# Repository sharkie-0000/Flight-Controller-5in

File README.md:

# 5-Inch Autonomous Wall-Inspection Flight Controller

A custom 4-layer drone flight controller designed for autonomous infrastructure inspection (inspecting building facades, concrete structures, bridges, and industrial indoor spaces where GPS is completely denied). It was a great way for me to explore high-speed embedded design, learn 4-layer PCB routing in KiCad, and solve real-world signal integrity and power challenges.

# How its works

This board is a custom-designed flight controller for autonomous GPS-denied drone navigation. It is based on the 480MHz ARM Cortex-M7 STM32H743VIT6 microcontroller and industrial-grade low-noise sensors.

- **Power & Protection:** Accepts 3S–6S LiPo battery power. An SMBJ28A TVS clamp and low-ESR bulk capacitance protect against motor regenerative braking spikes. A TPS54302 synchronous buck converter steps down to 5V @ 3A, while a dedicated ultra-low-noise MIC5219-3.3 LDO isolates sensitive sensor rails from switching noise.
- **Processing & Memory:** The STM32H743VIT6 serves as the main brain. It runs at 480MHz from an external 25MHz crystal, backed by a W25Q128 16MB SPI NOR Flash chip for high-rate Blackbox flight logging.
- **Dual-Navigation & Sensing:** Features an ICM-42688-P 6-axis IMU over high-speed SPI1 and a DPS310 barometer over I2C1. For indoor GPS-denied flight, dedicated ports connect a forward-facing Time-of-Flight (ToF) LiDAR for wall standoff tracking and a downward Optical Flow camera for hover holding.
- **Actuation & Companion Link:** Connects to standard 4-in-1 ESCs via DShot600 motor outputs (`MOTOR1`–`4`). A high-speed MAVLink UART communicates with an onboard companion computer (Raspberry Pi / NVIDIA Jetson), while an onboard 2N7002 MOSFET circuit synchronously triggers an inspection camera shutter or strobe.

```text
[ LiPo 3S-6S ] ──► [ SMBJ28A TVS ] ──► [ TPS54302 Buck (5V 3A) ] ──5V──► [ MIC5219 (3.3V LDO) ] ──3.3V──┐
                                                 │                                                         ▼
                                          5V Peripherals                                            [ STM32H743 ]
                                                 │                                                   (480MHz MCU)
                                                 │                                                         │
   ┌───────────────────────┬─────────────────────┼─────────────────────────┬───────────────────────────────┤
   │ (SPI1)                │ (I2C1)              │ (SPI2)                  │ (UARTs)                       │ (TIM PWM)
   ▼                       ▼                     ▼                         ▼                               ▼
[ ICM-42688-P ]       [ DPS310 ]            [ W25Q128 ]          [ Forward Wall ToF ]               [ 4-in-1 ESC ]
  (6-Axis IMU)         (Baro)               (Blackbox)           [ Downward Flow    ]               (DShot Motors)
                                                                 [ Outdoor GPS/Mag  ]
                                                                 [ Jetson / Pi MAV  ]
                                                                 [ ELRS Receiver    ]
```

# Images:

## 3d

## Schematic

## PCB

## Components

- **Total Physical Components:** 51
- **Capacitors:** 24 (Bulk 470µF electrolytic, 22µF, 10µF, 2.2µF VCAP, 100nF decoupling, 18pF crystal caps)
- **Resistors:** 8 (Precision 0.1% voltage divider, USB-C 5.1k pull-downs, I2C 2.2k pull-ups)
- **Inductor:** 1 (4.7µH 4.5A shielded power inductor)
- **Crystals / Oscillators:** 1 (25.000MHz HSE crystal)
- **Microcontroller:** 1 (STM32H743VIT6 ARM Cortex-M7 LQFP-100)
- **Sensors:** 2 (ICM-42688-P 6-axis IMU, DPS310 precision barometer)
- **Memory:** 1 (W25Q128 16MB SPI NOR Flash)
- **Power ICs:** 2 (TPS54302 5V 3A buck converter, MIC5219-3.3 low-noise LDO)
- **MOSFETs / Diodes:** 3 (SMBJ28A TVS clamp, 2x 2N7002 N-channel FETs for buzzer & camera strobe)
- **Connectors / Headers:** 8 (USB-C 16-pin, JST-SH 8-pin ESC, JST-SH 6-pin GPS, 3x JST-SH 4-pin for ToF/Flow/MAVLink, SWD header, Buzzer pads)
- **Bare PCB Fabrication:** 5x 4-layer FR-4 boards (JLCPCB 36x36mm, JLC04161H-7628 stackup)

## BOM

| Qty | Component | Selected Part | Supplier | LCSC Part Number | Unit Price (USD) | Order Cost (USD) |
| :-: | :--- | :--- | :-: | :-: | --: | --: |
| 1 | STM32H743VIT6 MCU (Cortex-M7 480MHz, 2MB Flash, LQFP-100) | STM32H743VIT6 | LCSC | [C143110](https://www.lcsc.com/product-detail/C143110.html) | $11.20 | $11.20 |
| 1 | ICM-42688-P 6-Axis Low-Noise IMU (LGA-14) | ICM-42688-P | LCSC | [C2842426](https://www.lcsc.com/product-detail/C2842426.html) | $2.85 | $2.85 |
| 1 | DPS310 High-Precision Barometer (8-LGA) | DPS310XTSA1 | LCSC | [C155453](https://www.lcsc.com/product-detail/C155453.html) | $1.45 | $1.45 |
| 1 | W25Q128 16MB SPI NOR Flash (SOIC-8) | W25Q128JVSIQ | LCSC | [C97521](https://www.lcsc.com/product-detail/C97521.html) | $0.65 | $0.65 |
| 1 | TPS54302 5V 3A Synchronous Buck Converter (SOT-23-6) | TPS54302DDCR | LCSC | [C115848](https://www.lcsc.com/product-detail/C115848.html) | $0.72 | $0.72 |
| 1 | MIC5219-3.3 Ultra-Low-Noise LDO (SOT-23-5) | MIC5219-3.3YM5 | LCSC | [C7899](https://www.lcsc.com/product-detail/C7899.html) | $0.38 | $0.38 |
| 1 | SMBJ28A TVS Diode Clamp 600W (SMB) | SMBJ28A | LCSC | [C8536](https://www.lcsc.com/product-detail/C8536.html) | $0.12 | $0.12 |
| 1 | 4.7uH 4.5A Shielded Power Inductor (SMD 7x7mm) | NR8040T4R7N | LCSC | [C10452](https://www.lcsc.com/product-detail/C10452.html) | $0.35 | $0.35 |
| 1 | 25.000MHz High-Speed External Crystal (3225) | X322525MOB4SI | LCSC | [C9002](https://www.lcsc.com/product-detail/C9002.html) | $0.18 | $0.18 |
| 2 | 2N7002 N-Channel MOSFET 60V 300mA (SOT-23) | 2N7002 | LCSC | [C8502](https://www.lcsc.com/product-detail/C8502.html) | $0.04 | $0.08 |
| 1 | USB-C 16-Pin Receptacle (SMD+DIP) | TYPE-C-31-M-12 | LCSC | [C165948](https://www.lcsc.com/product-detail/C165948.html) | $0.28 | $0.28 |
| 1 | JST-SH 8-Pin Horizontal 1.0mm (4-in-1 ESC) | SM08B-SRSS-TB | LCSC | [C160404](https://www.lcsc.com/product-detail/C160404.html) | $0.22 | $0.22 |
| 1 | JST-SH 6-Pin Horizontal 1.0mm (GPS/Compass) | SM06B-SRSS-TB | LCSC | [C160403](https://www.lcsc.com/product-detail/C160403.html) | $0.18 | $0.18 |
| 2 | JST-SH 4-Pin Horizontal 1.0mm (ToF & RC) | SM04B-SRSS-TB | LCSC | [C160401](https://www.lcsc.com/product-detail/C160401.html) | $0.15 | $0.30 |
| 1 | JST-SH 4-Pin Horizontal 1.0mm (Optical Flow) | SM04B-SRSS-TB | LCSC | [C160401](https://www.lcsc.com/product-detail/C160401.html) | $0.15 | $0.15 |
| 1 | JST-SH 4-Pin Horizontal 1.0mm (MAVLink Jetson) | SM04B-SRSS-TB | LCSC | [C160401](https://www.lcsc.com/product-detail/C160401.html) | $0.15 | $0.15 |
| 1 | 470uF 35V Low-ESR Bulk Electrolytic Capacitor | Radial Low-ESR | LCSC | [C134444](https://www.lcsc.com/product-detail/C134444.html) | $0.25 | $0.25 |
| 2 | 22uF 10V Ceramic Capacitor (0805 X5R) | 22uF 10V 0805 | LCSC | [C45783](https://www.lcsc.com/product-detail/C45783.html) | $0.05 | $0.10 |
| 1 | 10uF 50V Ceramic Capacitor (1206 X7R) | 10uF 50V 1206 | LCSC | [C13585](https://www.lcsc.com/product-detail/C13585.html) | $0.08 | $0.08 |
| 2 | 2.2uF 10V Ceramic Capacitor (0603 X7R - VCAP) | 2.2uF 10V 0603 | LCSC | [C23630](https://www.lcsc.com/product-detail/C23630.html) | $0.03 | $0.06 |
| 14 | 100nF 16V Ceramic Decoupling Capacitor (0402 X7R) | 100nF 16V 0402 | LCSC | [C1525](https://www.lcsc.com/product-detail/C1525.html) | $0.005 | $0.07 |
| 2 | 18pF 50V Crystal Load Capacitor (0402 C0G) | 18pF 50V 0402 | LCSC | [C1549](https://www.lcsc.com/product-detail/C1549.html) | $0.005 | $0.01 |
| 1 | 10k 0.1% Precision Voltage Divider Resistor (0603) | 10k 0.1% 0603 | LCSC | [C25744](https://www.lcsc.com/product-detail/C25744.html) | $0.03 | $0.03 |
| 1 | 1.0k 0.1% Precision Voltage Divider Resistor (0603) | 1.0k 0.1% 0603 | LCSC | [C25741](https://www.lcsc.com/product-detail/C25741.html) | $0.03 | $0.03 |
| 2 | 5.1k 1% USB-C CC Pulldown Resistor (0402) | 5.1k 1% 0402 | LCSC | [C25905](https://www.lcsc.com/product-detail/C25905.html) | $0.004 | $0.01 |
| 2 | 2.2k 1% I2C Bus Pullup Resistor (0402) | 2.2k 1% 0402 | LCSC | [C25879](https://www.lcsc.com/product-detail/C25879.html) | $0.004 | $0.01 |
| 2 | LED 0805 SMD (Blue Power / Green Armed) | LED 0805 | LCSC | [C84256](https://www.lcsc.com/product-detail/C84256.html) | $0.02 | $0.04 |
| 1 | 5V Active Buzzer Header / Pads | PinHeader 1x02 1.27mm | LCSC | [C2938](https://www.lcsc.com/product-detail/C2938.html) | $0.05 | $0.05 |
| 1 | Camera Shutter / Strobe Header | PinHeader 1x03 2.54mm | LCSC | [C2337](https://www.lcsc.com/product-detail/C2337.html) | $0.08 | $0.08 |
| 1 | SWD Debug Header | PinHeader 1x04 1.27mm | LCSC | [C2939](https://www.lcsc.com/product-detail/C2939.html) | $0.10 | $0.10 |
| 5 | Custom 4-Layer PCB (36x36mm, JLCPCB JLC04161H-7628 Stackup) | Custom PCB | JLCPCB | [JLCPCB](https://jlcpcb.com) | $1.00 | $5.00 |
| **—** | **Total Components Cost** | | **LCSC** | | | **$20.18** |
| **—** | **Total Procurement Cost (Components + 5x PCBs)** | | **LCSC + JLCPCB** | | | **~$25.18** |

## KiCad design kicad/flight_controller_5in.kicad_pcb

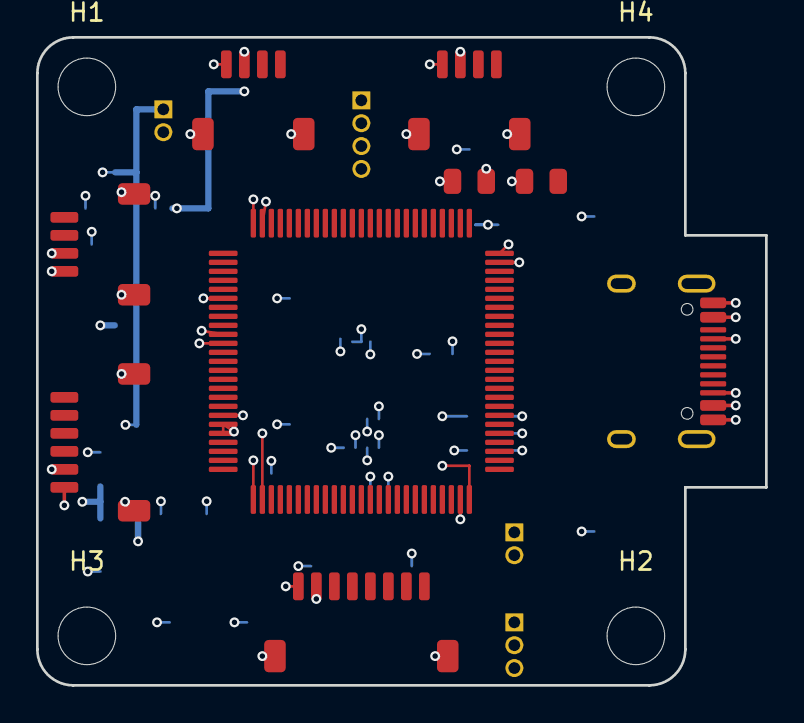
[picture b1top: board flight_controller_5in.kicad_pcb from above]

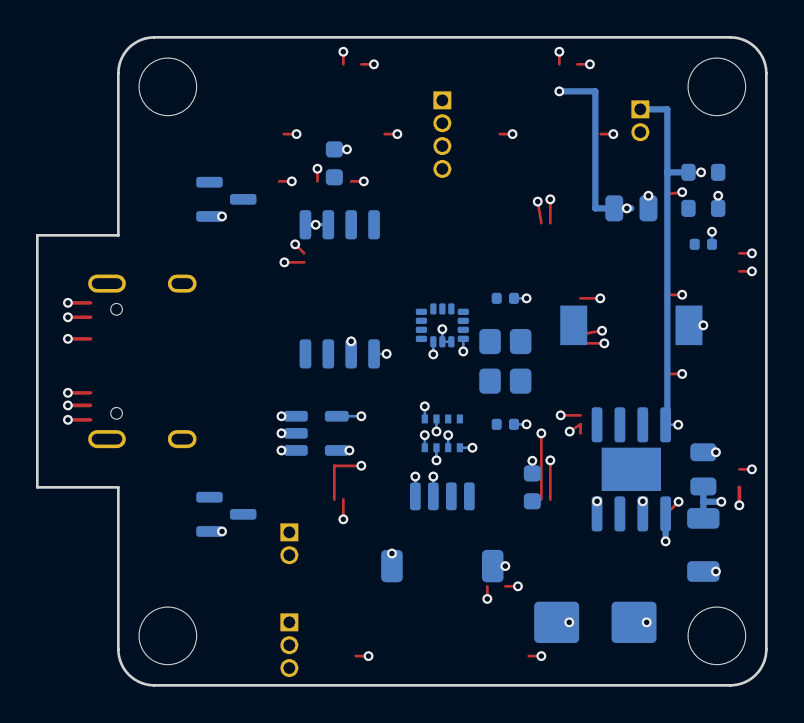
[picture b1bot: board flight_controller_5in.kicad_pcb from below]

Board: 4 copper layers, 40.5 x 36.0 mm, 38 parts (24 on the bottom side), 46 nets.

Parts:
BZ1: Buzzer Pads; PinHeader_1x02_P1.27mm_Vertical
C1: 22uF 50V Bulk; C_1206_3216Metric
C2: 10uF 50V; C_0805_2012Metric
C3: 22uF 10V; C_0805_2012Metric
C7: 100nF ADC; C_0402_1005Metric
C9, C10: 18pF; C_0402_1005Metric
C11: 2.2uF VCAP1; C_0603_1608Metric
C12: 2.2uF VCAP2; C_0603_1608Metric
D1: SMBJ28A TVS; D_SMB
D2: Blue 3.3V; LED_0805_2012Metric
D3: Green Armed; LED_0805_2012Metric
H1, H2, H3, H4: M3; MountingHole_3.2mm_M3
J_BAT: VBAT Pads; PinHeader_1x02_P1.27mm_Vertical
J_ESC: 4-in-1 ESC; JST_SH_SM08B-SRSS-TB_1x08-1MP_P1.00mm_Horizontal
J_FLOW: Optical Flow; JST_SH_SM04B-SRSS-TB_1x04-1MP_P1.00mm_Horizontal
J_GPS: GPS & Compass; JST_SH_SM06B-SRSS-TB_1x06-1MP_P1.00mm_Horizontal
J_MAVLINK: Companion MAVLink; JST_SH_SM04B-SRSS-TB_1x04-1MP_P1.00mm_Horizontal
J_RC: ELRS RC; JST_SH_SM04B-SRSS-TB_1x04-1MP_P1.00mm_Horizontal
J_STROBE: Camera Strobe; PinHeader_1x03_P1.27mm_Vertical
J_SWD: SWD Debug; PinHeader_1x04_P1.27mm_Vertical
J_USB: USB-C; USB_C_Receptacle_HRO_TYPE-C-31-M-12
J_WALL_TOF: ToF LiDAR; JST_SH_SM04B-SRSS-TB_1x04-1MP_P1.00mm_Horizontal
L1: 4.7uH Inductor; L_7.3x7.3_H3.5
Q1: 2N7002 Strobe; SOT-23
Q2: 2N7002 Buzzer; SOT-23
R1: 10k 0.1%; R_0603_1608Metric
R2: 1k 0.1%; R_0603_1608Metric
U1: TPS54302 (5V 3A); SOIC-8-1EP_3.9x4.9mm_P1.27mm_EP2.41x3.3mm
U2: MIC5219-3.3; SOT-23-5
U3: STM32H743VIT6; LQFP-100_14x14mm_P0.5mm
U4: ICM-42688-P; LGA-14_3x2.5mm_P0.5mm_LayoutBorder3x4y
U5: DPS310; Bosch_LGA-8_2x2.5mm_P0.65mm_ClockwisePinNumbering
U6: W25Q128 16MB; SOIC-8_5.3x5.3mm_P1.27mm
Y1: 25.0MHz; Crystal_SMD_3225-4Pin_3.2x2.5mm

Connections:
/+3V3: D2.2, U2.5, U3.6, U3.11, U3.20, U3.21, U3.27, U3.50, U3.75, U3.100, U4.5, U4.8, U5.2, U5.6, U5.8, U6.3, U6.7, U6.8
/+5V: BZ1.1, C3.1, J_FLOW.1, J_GPS.1, J_MAVLINK.1, J_RC.1, J_STROBE.1, J_USB.A4, J_USB.A9, J_USB.B4, J_USB.B9, J_WALL_TOF.1, L1.2, U1.4, U2.1, U2.3
/BUZZER_CTRL: Q2.1, U3.4
/BUZZER_NODE: BZ1.2, Q2.3
/CAM_STROBE_TRIG: Q1.1, U3.65
/CURR_SENSE: J_ESC.3, U3.17
/ESC_TLM: J_ESC.4, U3.38
/FLASH_CS: U3.51, U6.1
/FLOW_RX: J_FLOW.4, U3.56
/FLOW_TX: J_FLOW.3, U3.55
/GND: C1.2, C2.2, C3.2, C7.2, C9.2, C10.2, C11.2, C12.2, D1.2, D2.1, D3.1, J_BAT.2, J_ESC.1, J_ESC.MP, J_FLOW.2, J_FLOW.MP, J_GPS.2, J_GPS.MP, J_MAVLINK.2, J_MAVLINK.MP, J_RC.2, J_RC.MP, J_STROBE.3, J_SWD.4, J_USB.A1, J_USB.A5, J_USB.A12, J_USB.B1, J_USB.B5, J_USB.B12, J_USB.SH, J_WALL_TOF.2, J_WALL_TOF.MP, Q1.2, Q2.2, R2.2, U1.1, U2.2, U2.4, U3.10, U3.19, U3.26, U3.49, U3.74, U3.99, U4.6, U4.7, U5.1, U5.5, U5.7, U6.4
/GPS_RX: J_GPS.4, U3.23
/GPS_TX: J_GPS.3, U3.22
/I2C1_SCL: J_GPS.5, U3.95, U5.4
/I2C1_SDA: J_GPS.6, U3.96, U5.3
/IMU_CS: U3.34, U4.12
/IMU_INT1: U3.35, U4.4
/MAVLINK_RX: J_MAVLINK.4, U3.69
/MAVLINK_TX: J_MAVLINK.3, U3.68
/MOTOR1: J_ESC.5, U3.39
/MOTOR2: J_ESC.6, U3.41
/MOTOR3: J_ESC.7, U3.43
/MOTOR4: J_ESC.8, U3.44
/NRST: J_SWD.3, U3.14
/OSC_IN: C9.1, U3.12, Y1.1
/OSC_OUT: C10.1, U3.13, Y1.2
/RC_RX: J_RC.4, U3.64
/RC_TX: J_RC.3, U3.63
/SPI1_MISO: U3.30, U4.1
/SPI1_MOSI: U3.31, U4.14
/SPI1_SCK: U3.29, U4.13
/SPI2_MISO: U3.53, U6.2
/SPI2_MOSI: U3.54, U6.5
/SPI2_SCK: U3.52, U6.6
/STATUS_LED: D3.2, U3.2
/STROBE_OUT: J_STROBE.2, Q1.3
/SWCLK: J_SWD.2, U3.76
/SWDIO: J_SWD.1, U3.72
/SW_NODE: L1.1, U1.2
/USB_DM: J_USB.A7, J_USB.B7, U3.70
/USB_DP: J_USB.A6, J_USB.B6, U3.71
/VBAT: C1.1, C2.1, D1.1, J_BAT.1, J_ESC.2, R1.1, U1.3, U1.5
/VBAT_SENSE: C7.1, R1.2, R2.1, U3.16
/VCAP: C11.1, C12.1, U3.48, U3.73
/WALL_TOF_RX: J_WALL_TOF.4, U3.87
/WALL_TOF_TX: J_WALL_TOF.3, U3.86

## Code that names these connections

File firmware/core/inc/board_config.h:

#ifndef BOARD_CONFIG_H
#define BOARD_CONFIG_H

#include <stdint.h>
#include <stdbool.h>

/* Board Hardware Profile: 5-inch Autonomous Wall-Inspection FC */
#define BOARD_NAME          "FC_5IN_INSPECTION_H7"
#define MCU_TYPE            "STM32H743VIT6"
#define HSE_VALUE           25000000UL /* 25 MHz External Crystal */
#define SYSCLK_FREQ         480000000UL

/* Pin Mappings */
/* Status LEDs */
#define LED_PWR_PIN         GPIO_PIN_2   /* Blue LED (3.3V) */
#define LED_ARM_PIN         GPIO_PIN_3   /* Green LED (Status/Armed) */
#define LED_PORT            GPIOD

/* SPI1 - ICM-42688-P IMU */
#define IMU_SPI             SPI1
#define IMU_CS_PIN          GPIO_PIN_4
#define IMU_CS_PORT         GPIOA
#define IMU_INT_PIN         GPIO_PIN_5
#define IMU_INT_PORT        GPIOC

/* I2C1 - DPS310 Barometer */
#define BARO_I2C            I2C1
#define BARO_SCL_PIN        GPIO_PIN_8
#define BARO_SDA_PIN        GPIO_PIN_9
#define BARO_PORT           GPIOB

/* SPI2 - W25Q128 Flash */
#define FLASH_SPI           SPI2
#define FLASH_CS_PIN        GPIO_PIN_12
#define FLASH_CS_PORT       GPIOB

/* Motor PWM / DShot (TIM1 / TIM4) */
#define MOTOR1_PIN          GPIO_PIN_9
#define MOTOR2_PIN          GPIO_PIN_11
#define MOTOR3_PIN          GPIO_PIN_13
#define MOTOR4_PIN          GPIO_PIN_14
#define MOTOR_PORT          GPIOE

/* Navigation & Peripherals */
#define TOF_UART            USART2       /* J_WALL_TOF */
#define FLOW_UART           UART4        /* J_FLOW */
#define GPS_UART            USART1       /* J_GPS */
#define MAVLINK_UART        USART3       /* J_MAVLINK */
#define RC_UART             UART7        /* J_RC (CRSF/ELRS) */

/* Strobe & Buzzer FET Outputs */
#define STROBE_PIN          GPIO_PIN_8   /* 2N7002 FET */
#define STROBE_PORT         GPIOC
#define BUZZER_PIN          GPIO_PIN_15  /* 2N7002 FET */
#define BUZZER_PORT         GPIOB

#endif /* BOARD_CONFIG_H */
